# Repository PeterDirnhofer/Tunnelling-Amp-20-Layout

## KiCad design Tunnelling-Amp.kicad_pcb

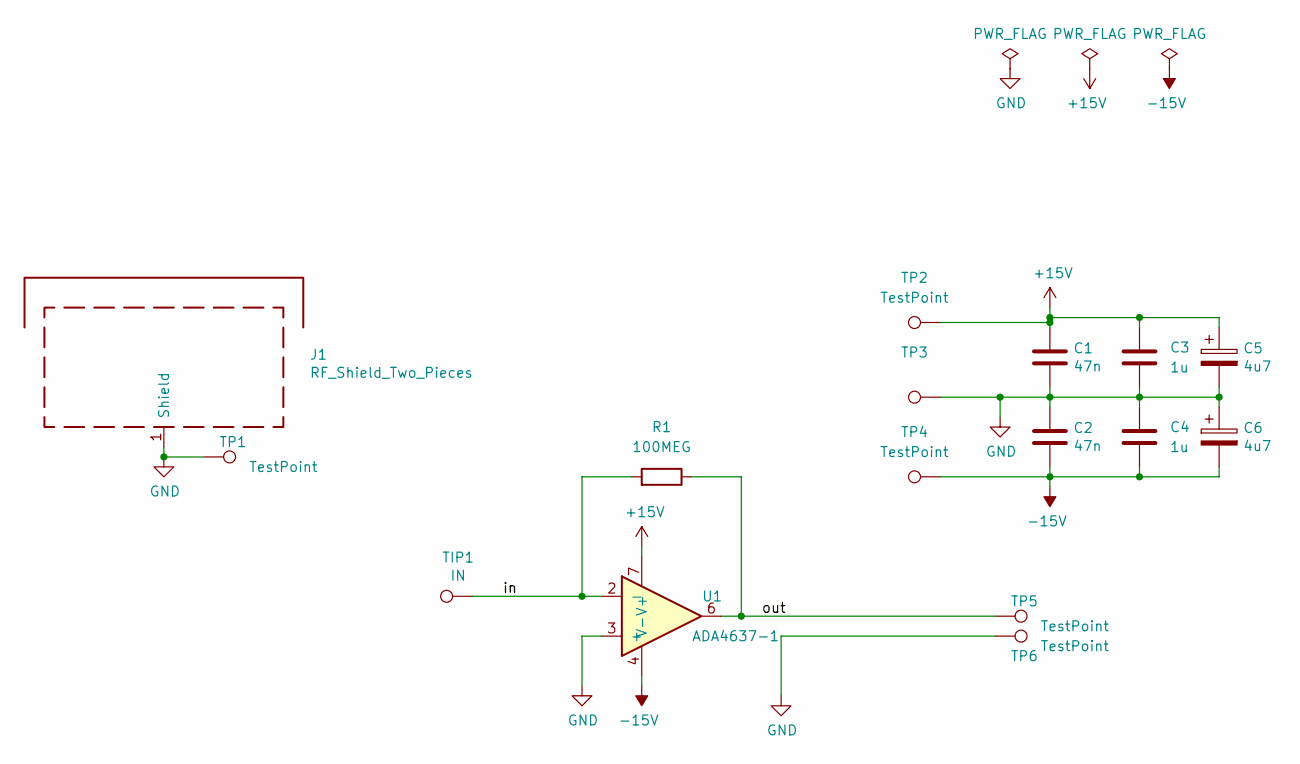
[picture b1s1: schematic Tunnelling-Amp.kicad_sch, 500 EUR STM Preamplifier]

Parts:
C1, C2: 47n; C_0805_2012Metric_Pad1.18x1.45mm_HandSolder
C3, C4: 1u; C_0805_2012Metric_Pad1.18x1.45mm_HandSolder
C5: 4u7; CP_EIA-6032-15_Kemet-U; Digikey 478-1737-1-ND
C6: 4u7; CP_EIA-6032-15_Kemet-U
J1: RF_Shield_Two_Pieces; Laird_Technologies_BMI-S-201-F_13.66x12.70mm; Digikey 903-1006-1-ND or 903-1050-1-ND + 903-10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
R1: 100MEG; R_1206_3216Metric_Pad1.30x1.75mm_HandSolder; Digikey 13-RC1206JR-07100MLCT-ND
TIP1: IN; TestPoint_Pad_2.5x2.5mm
TP1, TP2, TP3, TP4, TP5, TP6: TestPoint; TestPoint_Pad_D1.5mm
U1: ADA4637-1; SOIC-8_3.9x4.9mm_P1.27mm; Digikey ADA4637-1ARZ-ND

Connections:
+15V: C1.1, C3.1, C5.1, TP2.1, U1.7 (V+)
-15V: C2.2, C4.2, C6.2, TP4.1, U1.4 (V-)
/in: R1.2, TIP1.1, U1.2 (-)
/out: R1.1, TP5.1, U1.6
GND: C1.2, C2.1, C3.2, C4.1, C5.2, C6.1, J1.1 (Shield), TP1.1, TP3.1, TP6.1, U1.3 (+)

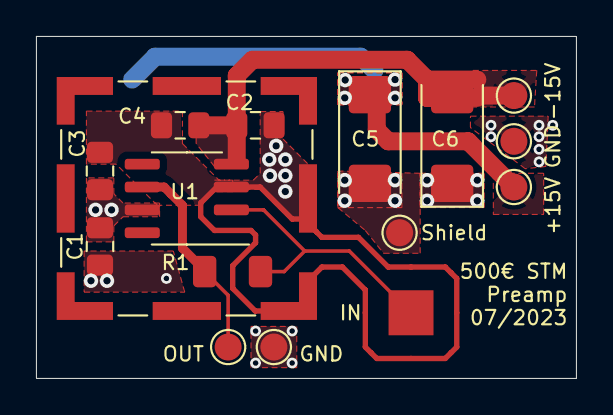
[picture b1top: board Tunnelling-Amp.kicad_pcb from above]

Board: 2 copper layers, 30.0 x 19.0 mm, 16 parts (0 on the bottom side), 5 nets.

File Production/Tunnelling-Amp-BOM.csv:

Id;Designator;Footprint;Quantity;Designation;Supplier and ref
1;C5,C6;CP_EIA-6032-15_Kemet-U;2;4u7;
2;TIP1;TestPoint_Pad_2.5x2.5mm;1;IN;
3;C3,C4;C_0805_2012Metric_Pad1.18x1.45mm_HandSolder;2;1u;
4;J1;Laird_Technologies_BMI-S-201-F_13.66x12.70mm;1;RF_Shield_Two_Pieces;
5;U1;SOIC-8_3.9x4.9mm_P1.27mm;1;ADA4637-1;
6;C1,C2;C_0805_2012Metric_Pad1.18x1.45mm_HandSolder;2;47n;
7;R1;R_1206_3216Metric_Pad1.30x1.75mm_HandSolder;1;100MEG;
8;TP2,TP1,TP5,TP6,TP3,TP4;TestPoint_Pad_D1.5mm;6;TestPoint;
